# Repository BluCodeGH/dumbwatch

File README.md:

# DumbWatch - An offline-first E-paper smartwatch

## Images

The final assembled watch.

Running a battery life and RTC test using a stand-in display.

Both sides of the custom PCB.

## Features

Dumbwatch is designed to be minimalist, with its most notable (anti-)feature being a lack of wireless connectivity. It still packs in a few nice-to-haves though:

- Two months of battery life on a 170 mAh LiPo
- LiPo charging over USB
- An E-paper dispay driver compatible with most common displays
- Communication over USB, e.g. for setting the time or loading your calendar for the day

The board is powered by the PIC18F27J53, which has an internal RTC connected to a 32.768 kHz watch crystal. I have not observed any noticble drift in the time thus far.

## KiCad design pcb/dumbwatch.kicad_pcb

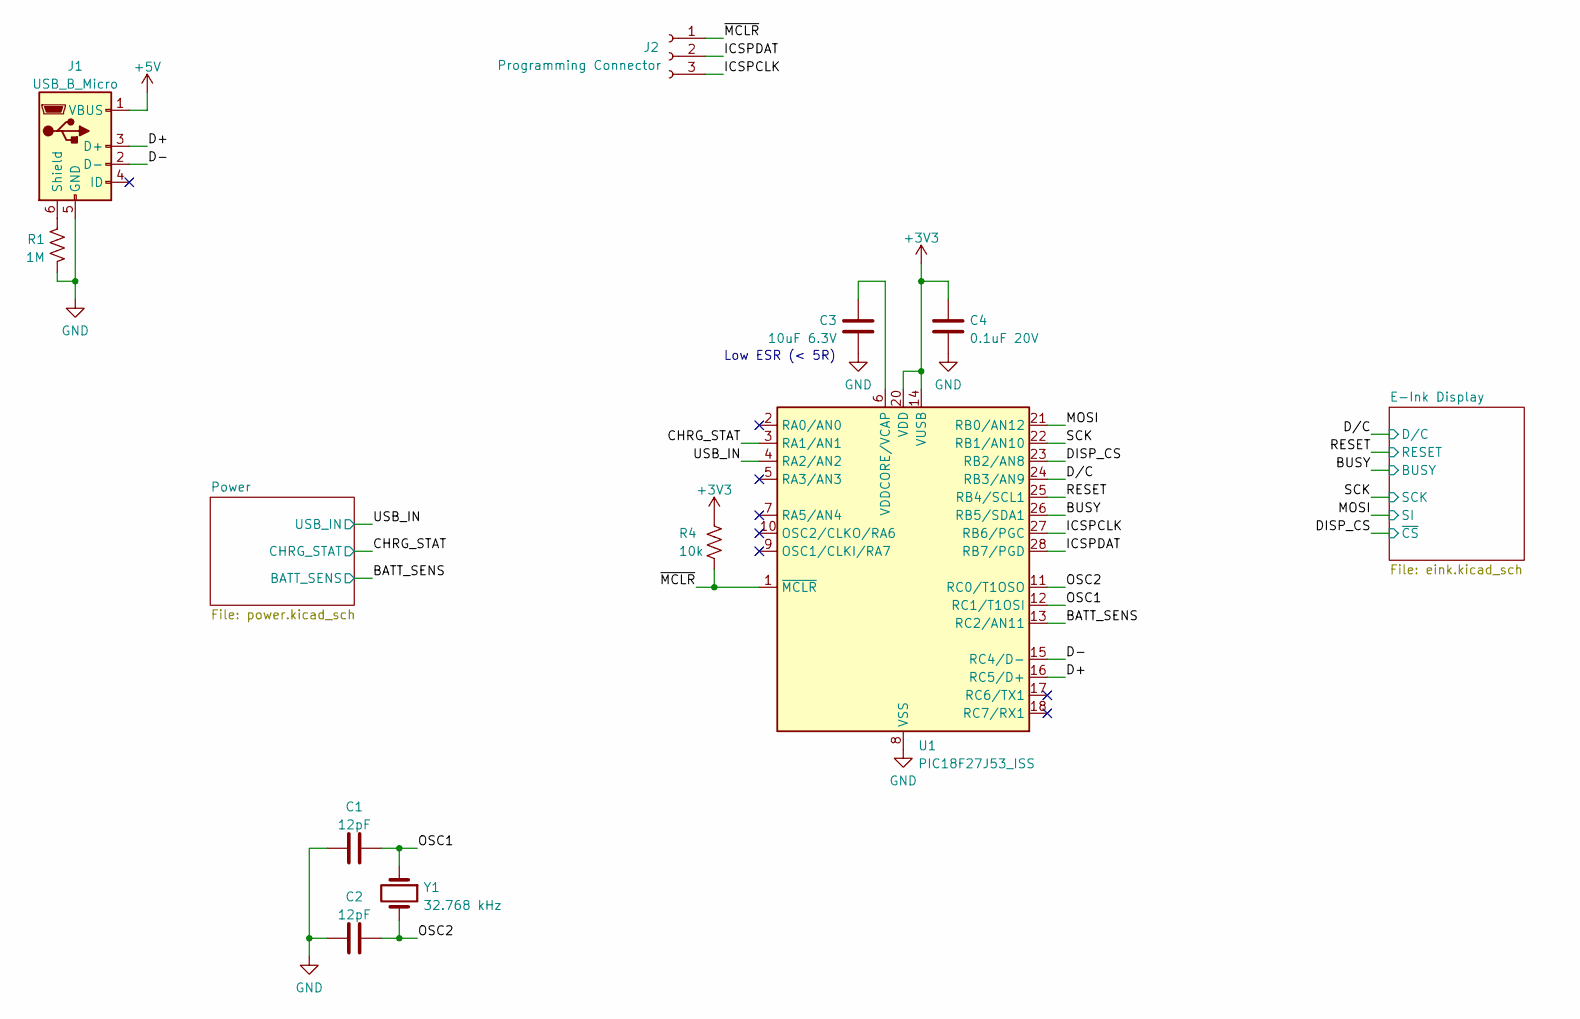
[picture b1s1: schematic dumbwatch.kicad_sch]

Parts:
C1, C2: 12pF; C_0805_2012Metric_Pad1.18x1.45mm_HandSolder
C3: 10uF 6.3V; C_0805_2012Metric_Pad1.18x1.45mm_HandSolder
C4: 0.1uF 20V; C_0805_2012Metric_Pad1.18x1.45mm_HandSolder
J1: USB_B_Micro; USB_Micro-B_Amphenol_10104110_Horizontal
J2: Programming Connector; PinHeader_3x2.54_SMD_90deg
R1: 1M; R_0805_2012Metric_Pad1.20x1.40mm_HandSolder
R4: 10k; R_0805_2012Metric_Pad1.20x1.40mm_HandSolder
U1: PIC18F27J53_ISS; SSOP-28_5.3x10.2mm_P0.65mm
Y1: 32.768 kHz; Crystal_SMD_MicroCrystal_MS3V-T1R

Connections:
+3V3: C4.2, R4.1, U1.14 (VUSB), U1.20 (VDD); also elsewhere on the board
+5V: J1.1 (VBUS); also elsewhere on the board
/BATT_SENS: U1.13 (RC2/AN11); also elsewhere on the board
/BUSY: U1.26 (RB5/SDA1); also elsewhere on the board
/CHRG_STAT: U1.3 (RA1/AN1); also elsewhere on the board
/D+: J1.3 (D+), U1.16 (RC5/D+)
/D-: J1.2 (D-), U1.15 (RC4/D-)
/DISP_CS: U1.23 (RB2/AN8); also elsewhere on the board
/D/C: U1.24 (RB3/AN9); also elsewhere on the board
/ICSPCLK: J2.3, U1.27 (RB6/PGC)
/ICSPDAT: J2.2, U1.28 (RB7/PGD)
/MOSI: U1.21 (RB0/AN12); also elsewhere on the board
/OSC1: C1.2, U1.12 (RC1/T1OSI), Y1.1
/OSC2: C2.2, U1.11 (RC0/T1OSO), Y1.2
/RESET: U1.25 (RB4/SCL1); also elsewhere on the board
/SCK: U1.22 (RB1/AN10); also elsewhere on the board
/USB_IN: U1.4 (RA2/AN2); also elsewhere on the board
/~MCLR: J2.1, R4.2, U1.1 (~MCLR)
GND: C1.1, C2.1, C3.1, C4.1, J1.5 (GND), R1.1, U1.8 (VSS), U1.19 (VSS); also elsewhere on the board
unnamed: C3.2, U1.6 (VDDCORE/VCAP)
unnamed: J1.6 (Shield), R1.2

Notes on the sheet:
Low ESR (< 5R)

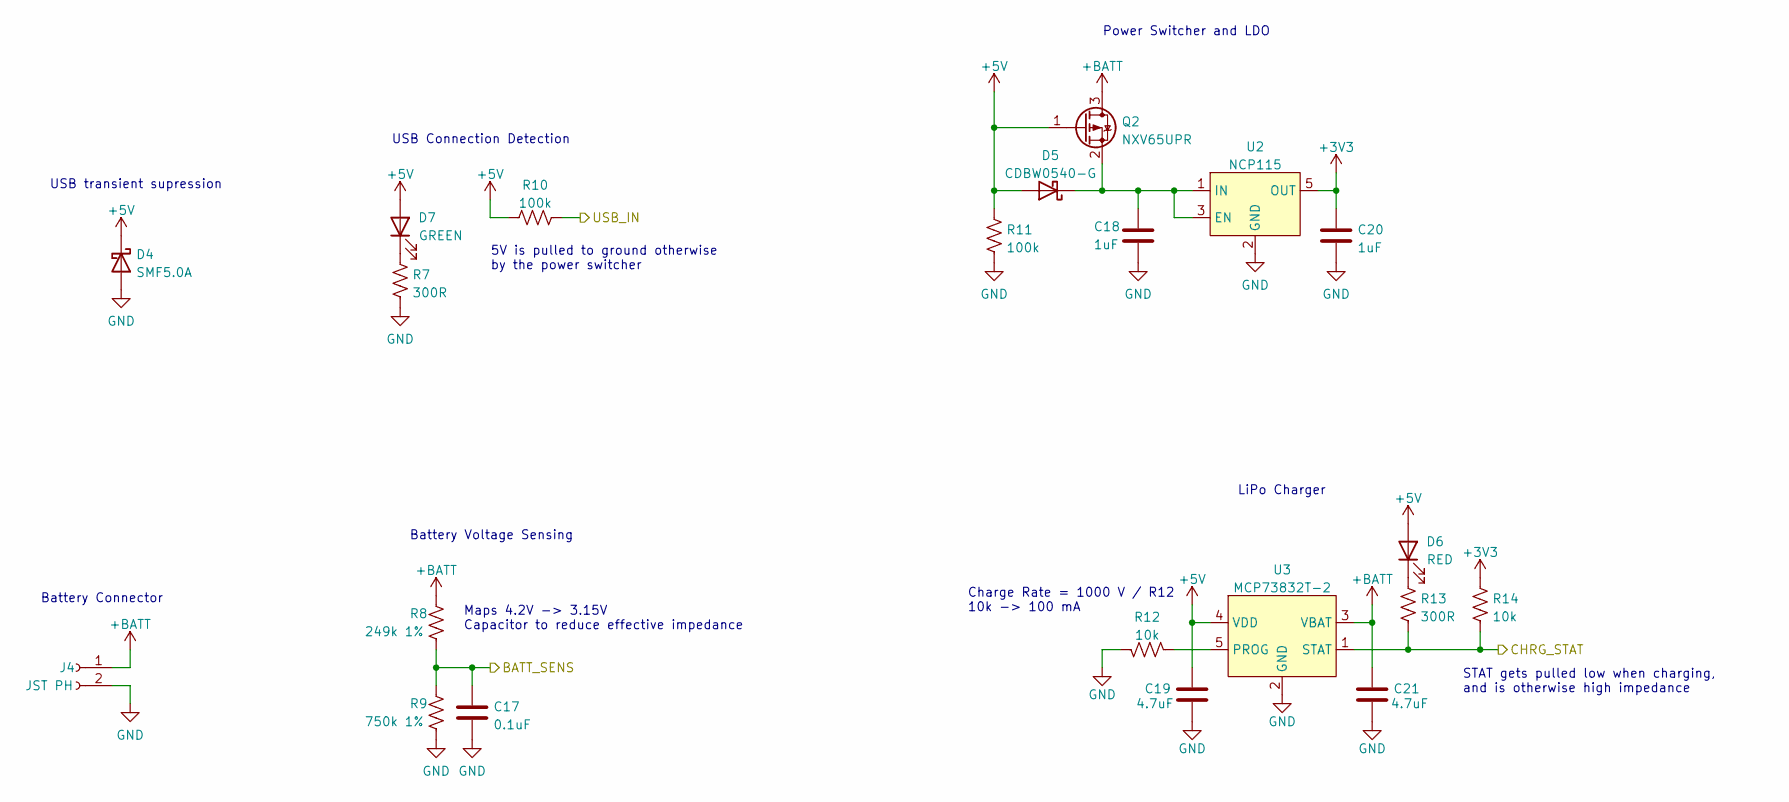
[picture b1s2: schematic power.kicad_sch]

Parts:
C17: 0.1uF; C_0805_2012Metric_Pad1.18x1.45mm_HandSolder
C18, C20: 1uF; C_0805_2012Metric_Pad1.18x1.45mm_HandSolder
C19, C21: 4.7uF; C_0805_2012Metric_Pad1.18x1.45mm_HandSolder
D4: SMF5.0A; D_SOD-123F
D5: CDBW0540-G; D_SOD-123
D6: RED; LED_1206_3216Metric_Pad1.42x1.75mm_HandSolder
D7: GREEN; LED_1206_3216Metric_Pad1.42x1.75mm_HandSolder
J4: JST PH; JST_PH_S2B-PH-K_1x02_P2.00mm_Horizontal
Q2: NXV65UPR; SOT-23
R7, R13: 300R; R_0805_2012Metric_Pad1.20x1.40mm_HandSolder
R8: 249k 1%; R_0805_2012Metric_Pad1.20x1.40mm_HandSolder
R9: 750k 1%; R_0805_2012Metric_Pad1.20x1.40mm_HandSolder
R10, R11: 100k; R_0805_2012Metric_Pad1.20x1.40mm_HandSolder
R12, R14: 10k; R_0805_2012Metric_Pad1.20x1.40mm_HandSolder
U2: NCP115; TSOT-23-5
U3: MCP73832T-2; SOT-23-5

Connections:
+3V3: C20.1, R14.1, U2.5 (OUT); also elsewhere on the board
+5V: C19.1, D4.1 (K), D5.2 (A), D6.2 (A), D7.2 (A), Q2.1 (G), R10.1, R11.1, U3.4 (VDD); also elsewhere on the board
+BATT: C21.1, J4.1, Q2.3 (D), R8.1, U3.3 (VBAT)
/BATT_SENS: C17.1, R8.2, R9.1; also elsewhere on the board
/CHRG_STAT: R13.2, R14.2, U3.1 (STAT); also elsewhere on the board
/USB_IN: R10.2; also elsewhere on the board
GND: C17.2, C18.2, C19.2, C20.2, C21.2, D4.2 (A), J4.2, R7.1, R9.2, R11.2, R12.2, U2.2 (GND), U3.2 (GND); also elsewhere on the board
unnamed: C18.1, D5.1 (K), Q2.2 (S), U2.1 (IN), U2.3 (EN)
unnamed: D6.1 (K), R13.1
unnamed: D7.1 (K), R7.2
unnamed: R12.1, U3.5 (PROG)

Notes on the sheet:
5V is pulled to ground otherwise by the power switcher
Battery Voltage Sensing
Charge Rate = 1000 V / R12 10k -> 100 mA
Maps 4.2V -> 3.15V Capacitor to reduce effective impedance
Battery Connector
USB Connection Detection
STAT gets pulled low when charging, and is otherwise high impedance
Power Switcher and LDO
USB transient supression
LiPo Charger

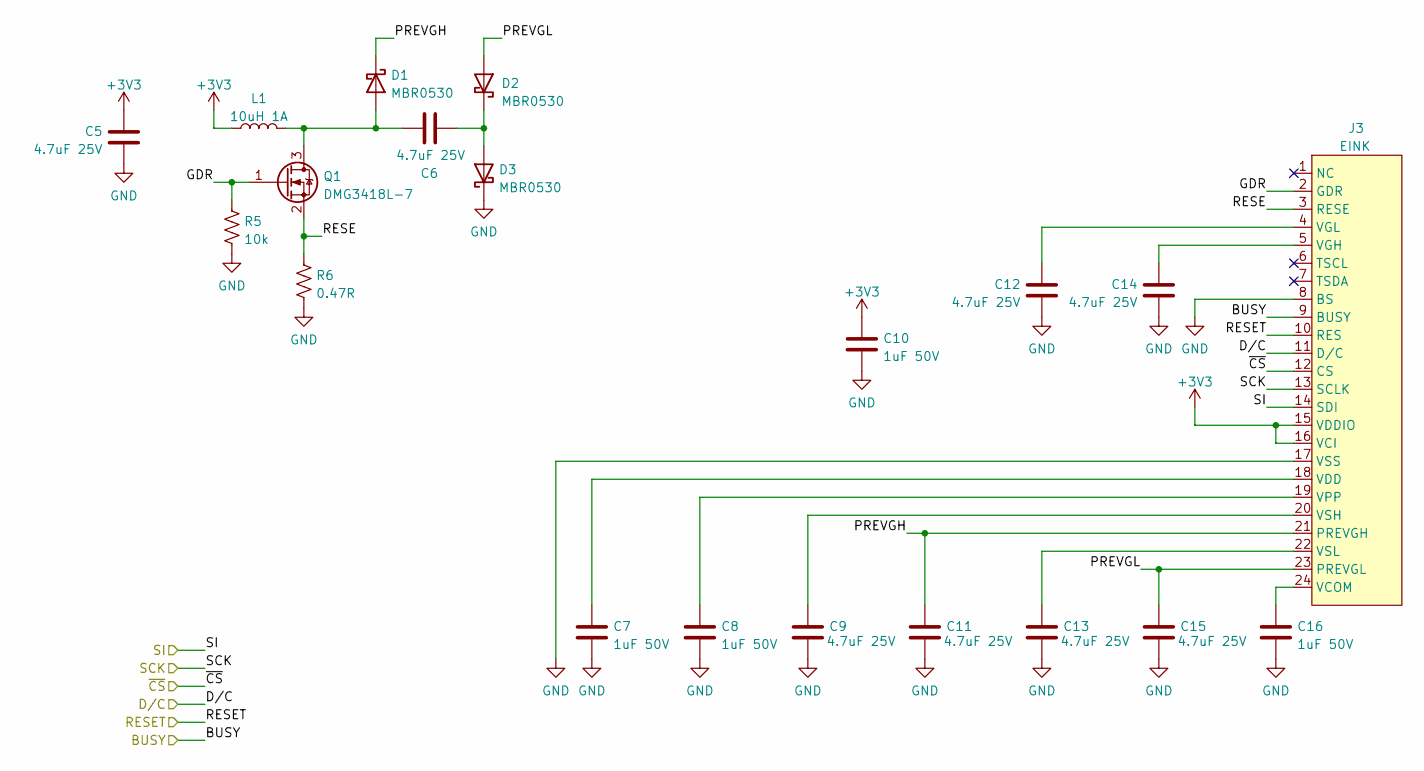
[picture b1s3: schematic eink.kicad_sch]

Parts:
C5, C6, C9, C11, C12, C13, C14, C15: 4.7uF 25V; C_0805_2012Metric_Pad1.18x1.45mm_HandSolder
C7, C8, C10, C16: 1uF 50V; C_0805_2012Metric_Pad1.18x1.45mm_HandSolder
D1, D2, D3: MBR0530; D_SOD-123
J3: EINK; Hirose_FH12-24S-0.5SH_1x24-1MP_P0.50mm_Horizontal
L1: 10uH 1A; L_1210_3225Metric_Pad1.42x2.65mm_HandSolder
Q1: DMG3418L-7; SOT-23
R5: 10k; R_0805_2012Metric_Pad1.20x1.40mm_HandSolder
R6: 0.47R; R_0805_2012Metric_Pad1.20x1.40mm_HandSolder

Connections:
+3V3: C5.1, C10.1, J3.15 (VDDIO), J3.16 (VCI), L1.1; also elsewhere on the board
/BUSY: J3.9 (BUSY); also elsewhere on the board
/DISP_CS: J3.12 (CS); also elsewhere on the board
/D/C: J3.11 (D/C); also elsewhere on the board
/E-Ink Display/GDR: J3.2 (GDR), Q1.1 (G), R5.1
/E-Ink Display/PREVGH: C11.1, D1.1 (K), J3.21 (PREVGH)
/E-Ink Display/PREVGL: C15.1, D2.2 (A), J3.23 (PREVGL)
/E-Ink Display/RESE: J3.3 (RESE), Q1.2 (S), R6.1
/MOSI: J3.14 (SDI); also elsewhere on the board
/RESET: J3.10 (RES); also elsewhere on the board
/SCK: J3.13 (SCLK); also elsewhere on the board
GND: C5.2, C7.2, C8.2, C9.2, C10.2, C11.2, C12.2, C13.2, C14.2, C15.2, C16.2, D3.1 (K), J3.8 (BS), J3.17 (VSS), R5.2, R6.2; also elsewhere on the board
unnamed: C6.1, D1.2 (A), L1.2, Q1.3 (D)
unnamed: C6.2, D2.1 (K), D3.2 (A)
unnamed: C7.1, J3.18 (VDD)
unnamed: C8.1, J3.19 (VPP)
unnamed: C9.1, J3.20 (VSH)
unnamed: C12.1, J3.4 (VGL)
unnamed: C13.1, J3.22 (VSL)
unnamed: C14.1, J3.5 (VGH)
unnamed: C16.1, J3.24 (VCOM)

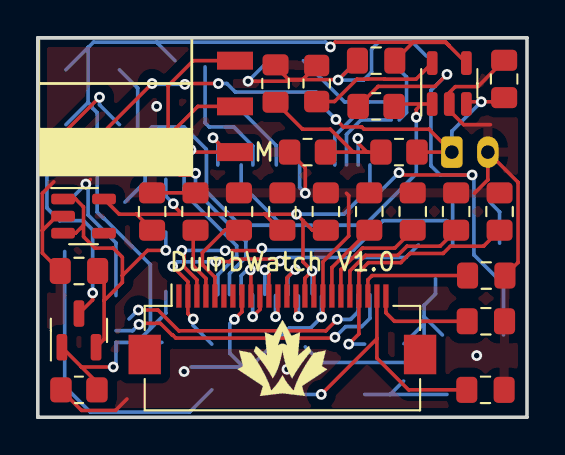
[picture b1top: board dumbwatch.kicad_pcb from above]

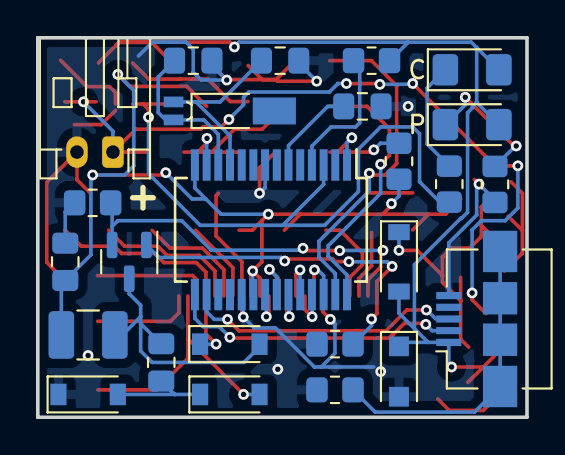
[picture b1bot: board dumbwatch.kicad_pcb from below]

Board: 2 copper layers, 27.2 x 21.1 mm, 51 parts (25 on the bottom side), 39 nets.

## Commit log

2022-10-03 Routing in progress with USB C connector
2022-10-23 PCB rev 1 complete
2022-10-23 Remove unused libraries
2022-10-23 Create LICENSE
2022-11-03 Rename hardware/ to pcb/
2022-11-03 First case prototype
2022-12-16 Get display, RTC working
2022-12-23 Firmware working
2023-01-05 Add images
2023-10-06 Update firmware for flexible e-paper
2024-04-13 Add assembled image
